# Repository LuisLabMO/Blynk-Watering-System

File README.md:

# Smart Modular Watering System using Blynk

I like plants, I like to be eco-friendly, love electronics, but how can I fit those things together? enters the **Smart Modular Watering System**.

Using the [SparkFun ESP8266 Blynk Board](https://www.sparkfun.com/products/13794) with the [Blynk app](http://www.blynk.cc) you can build a system that monitors the level of the water reservoir and will water your plants automatically at the right moment.

> **It will help you save water!**

## Sensors data

Data collected from sensors is used to decide when is the right time to water the plants, to send alerts when the water reservoir is low and more:

* **Soil moisture sensor**: accurately measures the actual soil moisture.
* An **ultrasonic distance sensor** will measure the level of the water reservoir with good reliability.
* **UV sensor** data may help deciding whether your plant needs more shadow or direct sunlight.
* **Temperature** and **humidity** sensors can also help deciding about critical conditions for your plants.

## Operation - The Blynk App

The Blynk app can be used to monitor in real time the data collected by the sensors:
* Plot the UV index.
* Monitor the water level, temperature, humidity, soil moisture in real time.
* Check the status of the irrigation system (On/Off) - **H2O Led**.

Some parameters of the system can be modified by using the Blynk app too:
* **Water level threshold**: if the water level is above¹ this number, the app will send a warning.
* **Soil moisture threshold**: the system will turn On the irrigation if the current soil moisture is below this number.
* **Watering interval _(in hours)_**: how often the system will irrigate -if conditions require it-.
* **Watering time _(in seconds)_**: duration of the irrigation when activated.

> ¹Please note that the water level sensor measures the distance between the top of the container and the surface of the water. So a higher number means a lower water level.

## Make it Modular, Make it Smarter

The **Smart Modular Watering System** has a very simple implementation, but there is lot of room for improvement. Some other features can be added to the **Smart Modular Watering System** with some more work, these are just a few examples:

* The **UV sensor** data can also be used to decide at what times of the day to stop watering. *Maybe stop watering at night?*
* The data collected can be analyzed to predict the water usage. e.g.: *How much water your plants will need before your next trip.*
* Add a solar panel, charge your batteries with it and show the world that you care about the Environment!.

## Repository Contents

* [/3D_Models](https://github.com/LuisLabMO/Blynk-Watering-System/tree/master/3D_Models) - SketchUp and **.STL** files
* [/ATtiny45_HC-SR04_to_I2C_Source_Code](https://github.com/LuisLabMO/Blynk-Watering-System/tree/master/ATtiny45_HC-SR04_to_I2C_Source_Code) - Source code for the ATtiny45 used to convert the data from ultrasonic distance sensor to I2C.
* [/Blynk_Board_Source_Code](https://github.com/LuisLabMO/Blynk-Watering-System/tree/master/Blynk_Board_Source_Code) - Source code for the [SparkFun ESP8266 Blynk Board](https://www.sparkfun.com/products/13794)
* [/Hardware](https://github.com/LuisLabMO/Blynk-Watering-System/tree/master/Hardware) - Eagle design files: **.BRD**, **.SCH**

## More Information

For more information visit the project page on [Hackster.io](https://www.hackster.io/lmortizg/smart-modular-watering-system-b571ec)

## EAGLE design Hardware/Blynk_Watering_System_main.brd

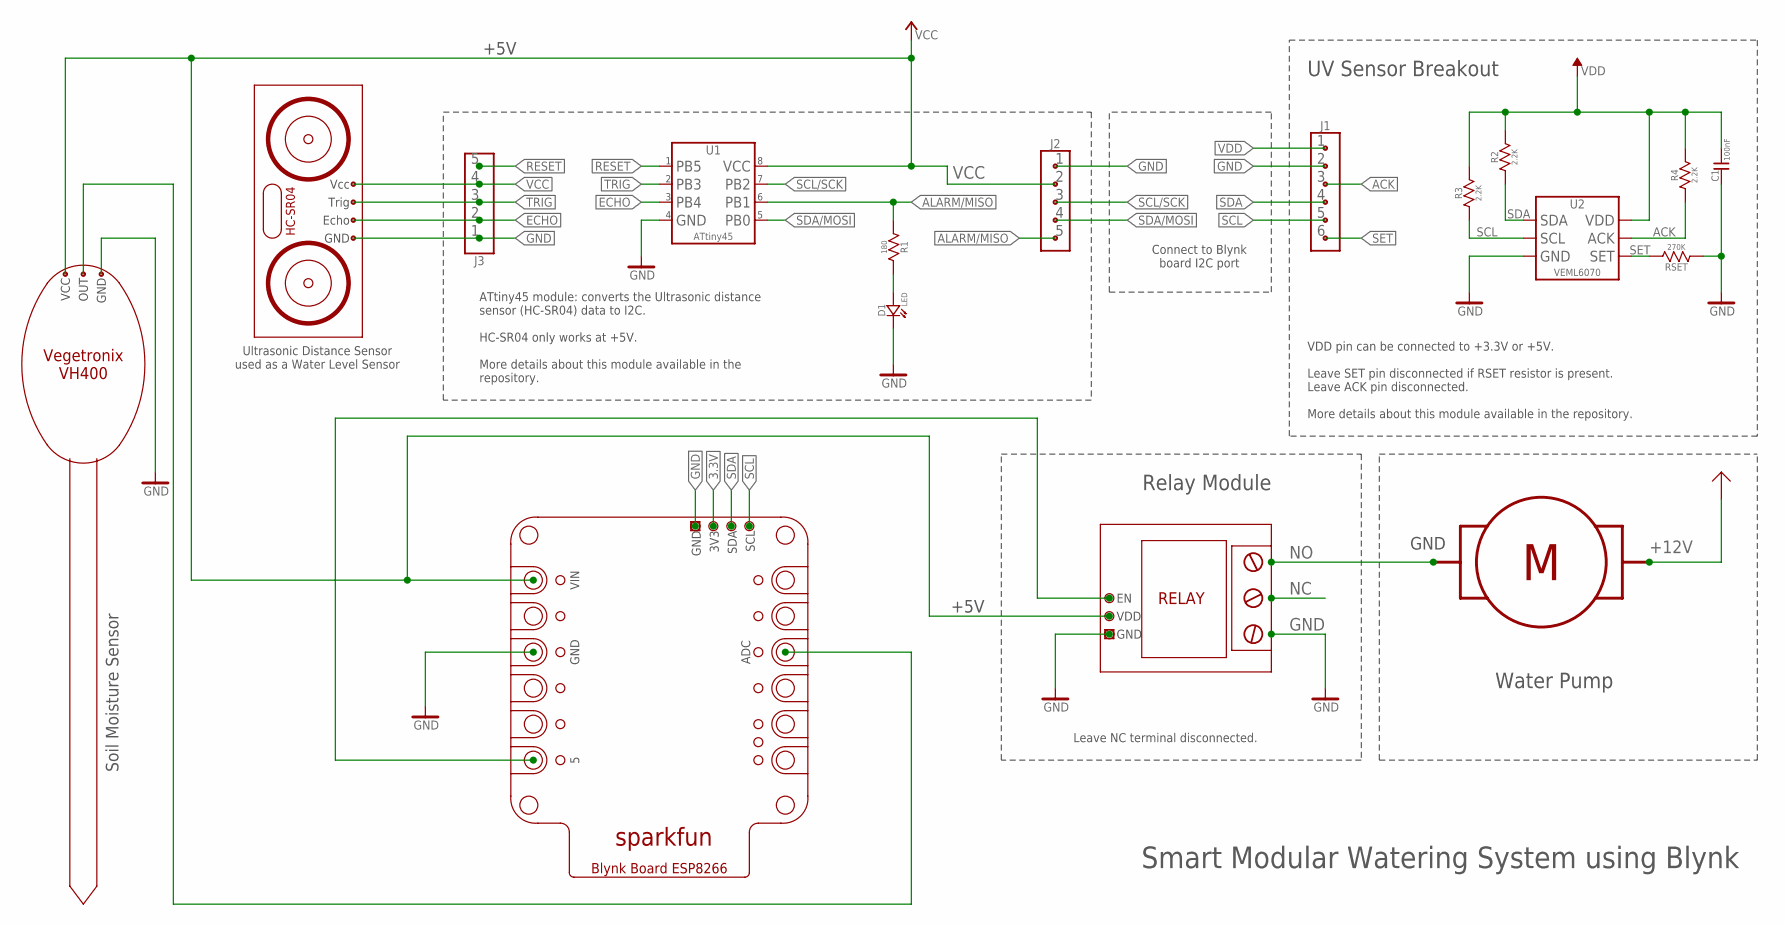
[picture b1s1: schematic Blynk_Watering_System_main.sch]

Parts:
C1: 100nF; 0603[1608]
D1: LED; 0805[2012]
J1: PIN_HEADER_1X06_0.1"_STR_G[2]_PTH
J2, J3: PIN_HEADER_1X05_0.1"_STR_G[1]_PTH
R1: 180; 0603[1608]
R2, R3, R4: 2.2K; 0603[1608]
RSET: 270K; 0603[1608]
U1: ATtiny45; TSSOP_MO-153-AC
U2: VEML6070; OPLGA

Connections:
ACK: J1.3, R4.1, U2.2 (ACK)
ALARM/MISO: J2.5, R1.1, U1.6 (PB1)
ECHO: J3.2, U1.3 (PB4)
GND: C1.1, D1.-, J1.2, J2.1, J3.1, RSET.1, U1.4 (GND), U2.1 (GND)
unnamed: D1.+, R1.2
RESET: J3.5, U1.1 (PB5)
SCL: J1.5, R3.1, U2.5 (SCL)
SCL/SCK: J2.3, U1.7 (PB2)
SDA: J1.4, R2.1, U2.3 (SDA)
SDA/MOSI: J2.4, U1.5 (PB0)
SET: J1.6, RSET.2, U2.4 (SET)
TRIG: J3.3, U1.2 (PB3)
VCC: J2.2, J3.4, U1.8 (VCC)
VDD: C1.2, J1.1, R2.2, R3.2, R4.2, U2.6 (VDD)

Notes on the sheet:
ATtiny45 module: converts the Ultrasonic distance sensor (HC-SR04) data to I2C. HC-SR04 only works at +5V. More details about this module available in the repository.
Vcc
Trig
Echo
GND
HC-SR04
VCC
OUT
Vegetronix VH400
Ultrasonic Distance Sensor used as a Water Level Sensor
Soil Moisture Sensor
VDD pin can be connected to +3.3V or +5V. Leave SET pin disconnected if RSET resistor is present. Leave ACK pin disconnected. More details about this module available in the repository.
sparkfun
Blynk Board ESP8266
ADC
VIN
SCL
SDA
3V3
UV Sensor Breakout
Connect to Blynk board I2C port
RELAY
VDD
+5V
Relay Module
Leave NC terminal disconnected.
Water Pump
Smart Modular Watering System using Blynk

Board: 2 copper layers, 12 parts (0 on the bottom side), 14 nets, no tracks yet.

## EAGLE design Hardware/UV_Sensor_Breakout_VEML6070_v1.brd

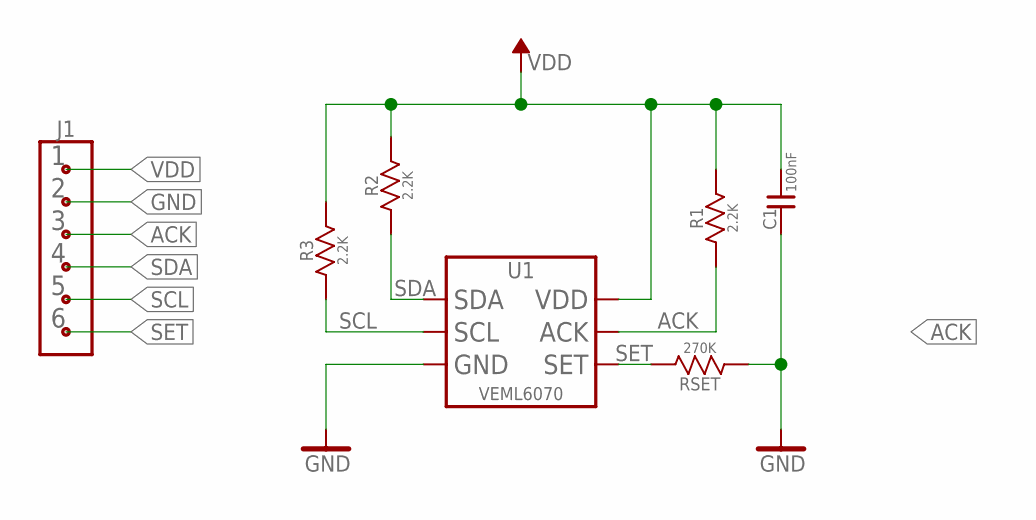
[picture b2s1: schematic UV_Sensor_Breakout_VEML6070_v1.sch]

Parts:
C1: 100nF; 0603[1608]
J1: PIN_HEADER_1X06_0.1"_STR_G[2]_PTH
R1, R2, R3: 2.2K; 0603[1608]
RSET: 270K; 0603[1608]
U1: VEML6070; OPLGA

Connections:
ACK: J1.3, R1.1, U1.2 (ACK)
GND: C1.1, J1.2, RSET.1, U1.1 (GND)
SCL: J1.5, R3.1, U1.5 (SCL)
SDA: J1.4, R2.1, U1.3 (SDA)
SET: J1.6, RSET.2, U1.4 (SET)
VDD: C1.2, J1.1, R1.2, R2.2, R3.2, U1.6 (VDD)

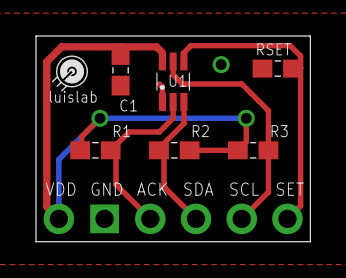
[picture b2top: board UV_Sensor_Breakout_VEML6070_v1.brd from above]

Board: 2 copper layers, 15.2 x 11.4 mm, 7 parts (1 on the bottom side), 6 nets.

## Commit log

2016-07-12 3D Models, Source code and eaglecad files created.
2016-07-12 Repository Contents updated
2016-07-12 "The Blynk app" contents added.
2016-07-12 minor fixes.
2016-07-12 minor fixes
2016-07-15 Added schematic .PDF
2016-07-15 Legend added
2016-07-16 Removed. Not required
2016-07-17 Added youtube video and Project link
2016-07-17 Fixed youtube thumbnail
2016-07-17 Removed thumbnail
2016-07-17 Changed thumbnail url. Github can't detect it is a new image.
